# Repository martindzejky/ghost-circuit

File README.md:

# Ghost Circuit

Made by following [these video tutorials](https://www.youtube.com/playlist?list=PL3bNyZYHcRSUhUXUt51W6nKvxx2ORvUQB).

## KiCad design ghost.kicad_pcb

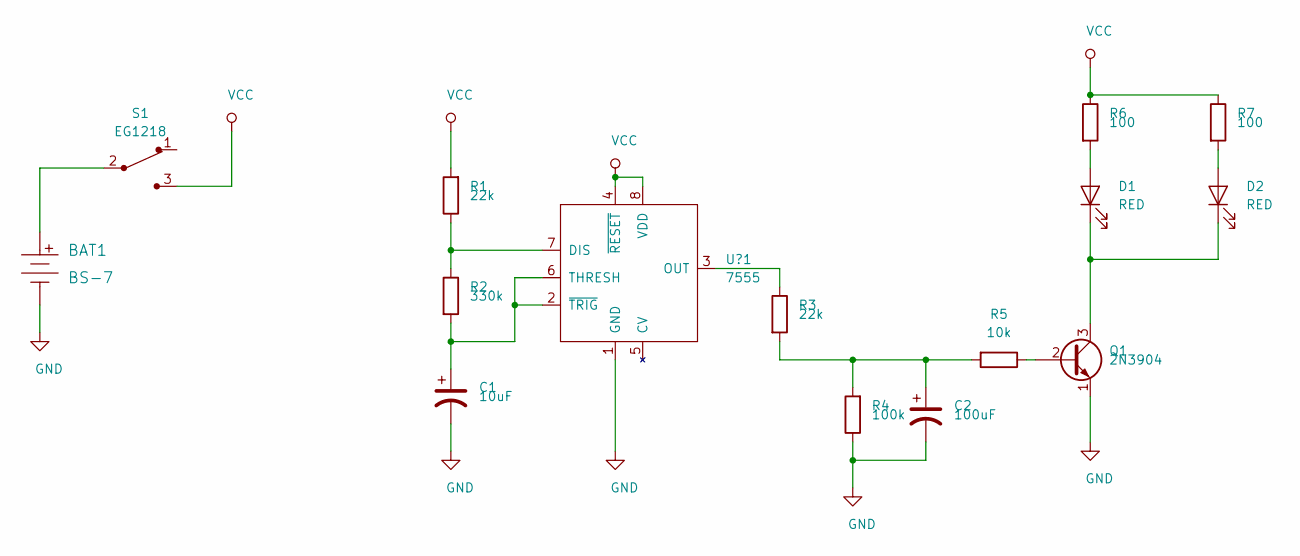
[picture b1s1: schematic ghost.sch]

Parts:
BAT1: BS-7; Battery_Holder_Coin_2032_BS-7; MPN BS-7; Digi-Key_PN BS-7-ND
C1: 10uF; CP_Radial_D5.0mm_P2.00mm
C2: 100uF; CP_Radial_D6.3mm_P2.50mm
D1, D2: RED; LED_D3.0mm
Q1: 2N3904; TO-92-3
R1, R3: 22k; R_Axial_DIN0207_L6.3mm_D2.5mm_P10.16mm_Horizontal
R2: 330k; R_Axial_DIN0207_L6.3mm_D2.5mm_P10.16mm_Horizontal
R4: 100k; R_Axial_DIN0207_L6.3mm_D2.5mm_P10.16mm_Horizontal
R5: 10k; R_Axial_DIN0207_L6.3mm_D2.5mm_P10.16mm_Horizontal
R6, R7: 100; R_Axial_DIN0207_L6.3mm_D2.5mm_P10.16mm_Horizontal
S1: EG1218; Switch_Slide_11.6x4mm_EG1218; MPN EG1218; Digi-Key_PN EG1903-ND
U?1: 7555; icm7555-pdip

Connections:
GND: BAT1.Neg, C1.2, C2.2, Q1.1 (E), R4.1, U?1.1 (GND); also elsewhere on the board
unnamed: BAT1.Pos, S1.2
unnamed 2: C1.1, R2.2, U?1.2 (~TRIG), U?1.6 (THRESH); also elsewhere on the board
unnamed: C2.1, R3.2, R4.2, R5.2
unnamed: D1.1 (K), D2.1 (K), Q1.3 (C)
unnamed: D1.2 (A), R6.2
unnamed: D2.2 (A), R7.2
unnamed: Q1.2 (B), R5.1
unnamed 8: R1.1, R2.1, U?1.7 (DIS); also elsewhere on the board
unnamed 9: R3.1, U?1.3 (OUT); also elsewhere on the board
VCC: R1.2, R6.1, R7.1, S1.3, U?1.4 (~RESET), U?1.8 (VDD); also elsewhere on the board

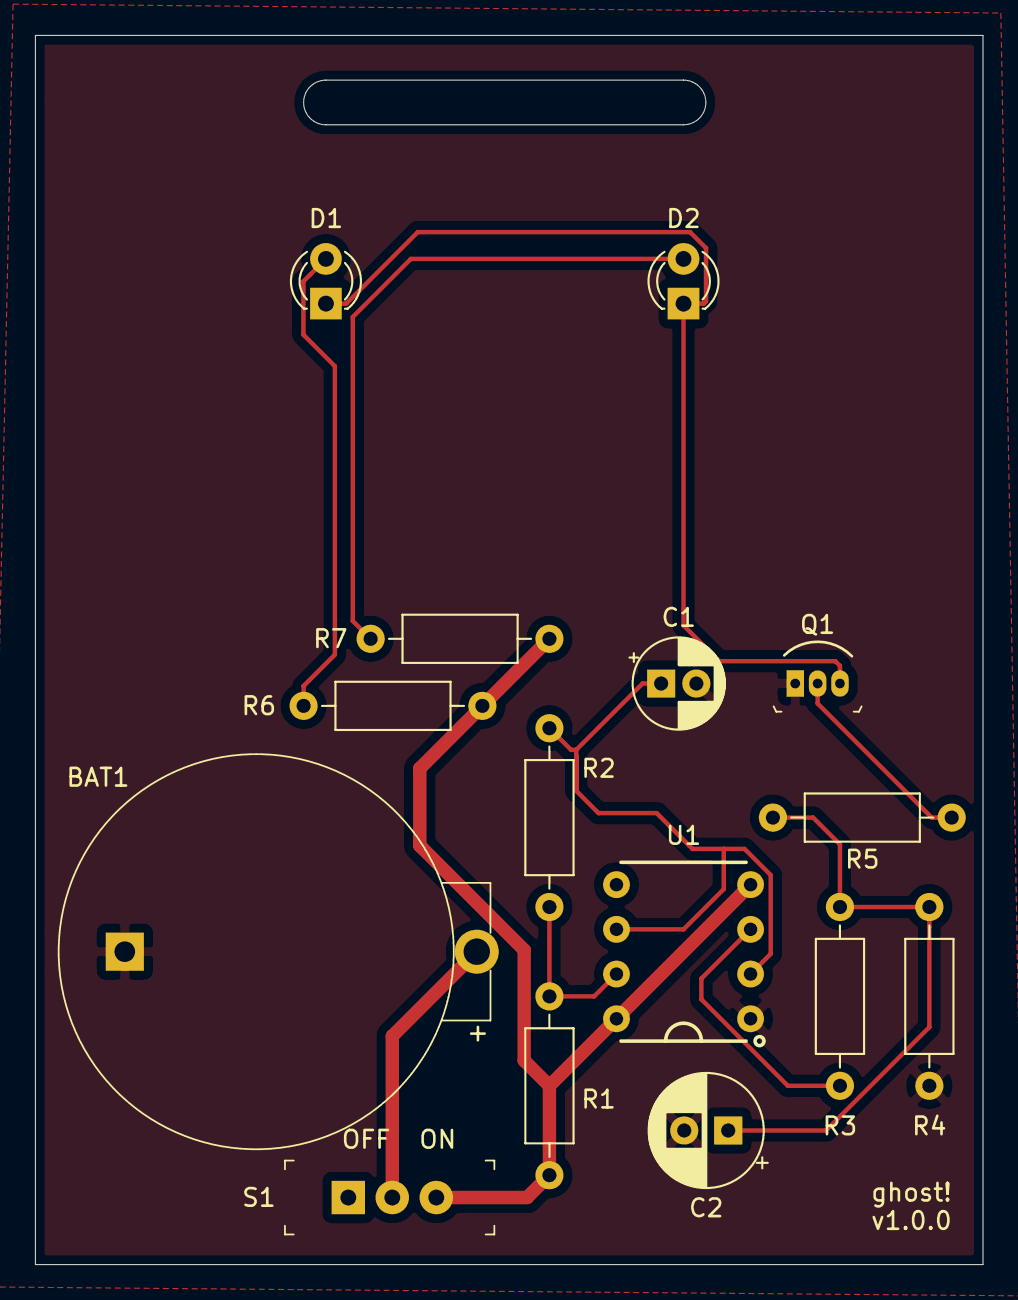
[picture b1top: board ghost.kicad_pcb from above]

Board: 2 copper layers, 53.8 x 69.8 mm, 15 parts (0 on the bottom side), 11 nets.

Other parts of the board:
U1: 7555; icm7555-pdip

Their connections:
GND: U1.1; also elsewhere on the board
unnamed 2: U1.2, U1.6; also elsewhere on the board
unnamed 8: U1.7; also elsewhere on the board
unnamed 9: U1.3; also elsewhere on the board
VCC: U1.4, U1.8; also elsewhere on the board

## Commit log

2019-12-18 add screenshots
2019-12-18 add images to README
